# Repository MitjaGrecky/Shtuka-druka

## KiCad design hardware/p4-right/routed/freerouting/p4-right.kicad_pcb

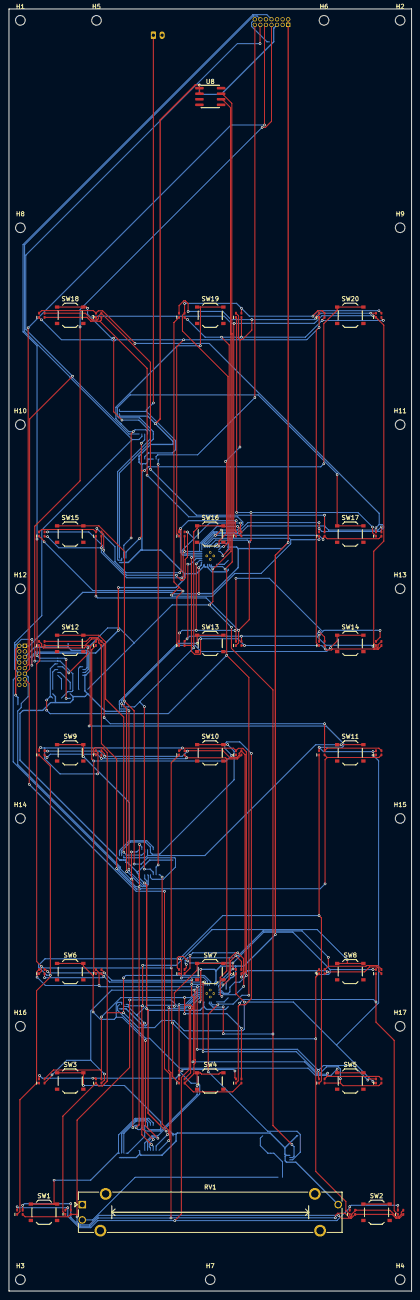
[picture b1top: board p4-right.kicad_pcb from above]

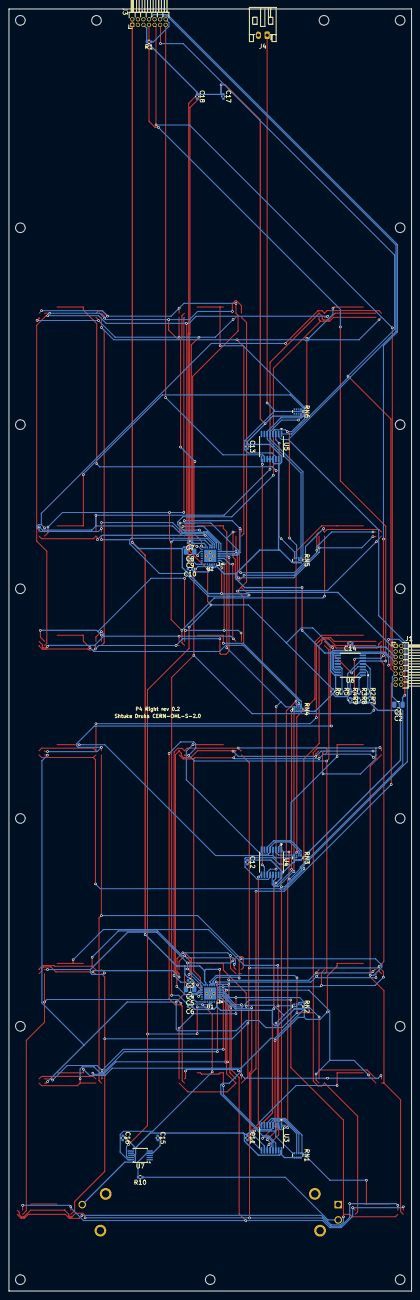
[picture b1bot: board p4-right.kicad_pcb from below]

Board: 2 copper layers, 92.0 x 293.0 mm, 123 parts (44 on the bottom side), 84 nets.

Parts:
C1: 10u; C_0805_2012Metric
C2, C3, C5, C7, C9, C18: 1u; C_0402_1005Metric
C4, C8: 4.7u; C_0805_2012Metric
C6, C10: 1n; C_0402_1005Metric
C11, C12, C13, C14, C15, C16, C17: 100n; C_0402_1005Metric
D1, D2, D3, D4, D5, D6, D7, D8, D9, D10, D11, D12, D13, D14, D15, D16, D17, D18, D19, D20, D21, D22, D23, D24, D25, D26, D27, D28, D29, D30, D31, D32, D33, D34, D35, D36, D37, D38, D39, D40: XL-1615RGBC-RF; LED_RGB_XL-1615RGBC_1.6x1.5mm
H1, H2, H3, H4, H5, H6, H7, H8, H9, H10, H11, H12, H13, H14, H15, H16, H17: M2; MountingHole_2.2mm_M2
J1: Deck bus to P2 2x8 1.27; PinHeader_2x08_P1.27mm_Horizontal
J3: Module bus to W3 2x7 1.27; PinHeader_2x07_P1.27mm_Horizontal
J4: Wheel push; JST_PH_S2B-PH-K_1x02_P2.00mm_Horizontal
R1, R2: 10k; R_0402_1005Metric
R3, R4, R5: 0; R_0402_1005Metric
R6, R7, R8, R9: 4.7k; R_0402_1005Metric
R10: 1k; R_0402_1005Metric
RN1, RN2, RN3, RN4, RN5, RN6: 4x10k; R_Array_Convex_4x0402
RV1: 10k lin, 45 mm travel; Potentiometer_Bourns_PTA4543_Single_Slide
SW1, SW2, SW3, SW4, SW5, SW6, SW7, SW8, SW9, SW10, SW11, SW12, SW13, SW14, SW15, SW16, SW17, SW18, SW19, SW20: TS-1187A-B-A-B; SW_Push_1P1T_XKB_TS-1187A
U1, U2: LP5864RSMR; VQFN-32-1EP_4x4mm_P0.4mm_EP2.8x2.8mm
U3, U4, U5: 74HC165PW; TSSOP-16_4.4x5mm_P0.65mm
U6: TCA9546APWR; TSSOP-16_4.4x5mm_P0.65mm
U7: ADS1115IDGSR; TSSOP-10_3x3mm_P0.5mm
U8: AS5600-ASOT; SOIC-8_3.9x4.9mm_P1.27mm

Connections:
+3V3: C2.1, C6.1, C10.1, C11.1, C12.1, C13.1, C14.1, C16.1, C17.1, C18.1, J1.5, J3.5, R1.2, R2.2, R4.2, R6.2, R7.2, R8.2, R9.2, RN1.5, RN1.6, RN1.7, RN1.8, RN2.5, RN2.6, RN2.7, RN2.8, RN3.5, RN3.6, RN3.7, RN3.8, RN4.5, RN4.6, RN4.7, RN4.8, RN5.5, RN5.6, RN5.7, RN5.8, RN6.8, RV1.3, U1.32, U2.30, U2.32, U3.16, U4.16, U5.11, U5.12, U5.13, U5.16, U6.16, U7.8, U8.1, U8.2
+5V: C1.1, C3.1, C4.1, C7.1, C8.1, J1.1, J1.2, J3.1, J3.2, U1.1, U1.15, U2.1, U2.15
/AIN0: C15.1, R10.2, U7.4
/A_CS0: D1.1, D2.1, D3.1, D4.1, U1.2
/A_CS1: D1.3, D2.3, D3.3, D4.3, U1.3
/A_CS2: D1.4, D2.4, D3.4, D4.4, U1.4
/A_CS3: D5.1, D6.1, D7.1, D8.1, U1.5
/A_CS4: D5.3, D6.3, D7.3, D8.3, U1.6
/A_CS5: D5.4, D6.4, D7.4, D8.4, U1.7
/A_CS6: D9.1, D10.1, D11.1, D12.1, U1.8
/A_CS7: D9.3, D10.3, D11.3, D12.3, U1.9
/A_CS8: D9.4, D10.4, D11.4, D12.4, U1.10
/A_CS9: D13.1, D14.1, D15.1, D16.1, U1.16
/A_CS10: D13.3, D14.3, D15.3, D16.3, U1.17
/A_CS11: D13.4, D14.4, D15.4, D16.4, U1.18
/A_CS12: D17.1, D18.1, D19.1, D20.1, U1.19
/A_CS13: D17.3, D18.3, D19.3, D20.3, U1.20
/A_CS14: D17.4, D18.4, D19.4, D20.4, U1.21
/A_CS15: D21.1, D22.1, D23.1, D24.1, U1.22
/A_CS16: D21.3, D22.3, D23.3, D24.3, U1.23
/A_CS17: D21.4, D22.4, D23.4, D24.4, U1.24
/A_SW0: D1.2, D5.2, D9.2, D13.2, D17.2, D21.2, U1.11
/A_SW1: D2.2, D6.2, D10.2, D14.2, D18.2, D22.2, U1.12
/A_SW2: D3.2, D7.2, D11.2, D15.2, D19.2, D23.2, U1.13
/A_SW3: D4.2, D8.2, D12.2, D16.2, D20.2, D24.2, U1.14
/A_VCAP: C5.1, U1.25
/BTN1: RN1.1, SW1.1, U3.6
/BTN2: RN1.2, SW2.1, U3.5
/BTN3: RN1.3, SW3.1, U3.4
/BTN4: RN1.4, SW4.1, U3.3
/BTN5: RN2.1, SW5.1, U3.14
/BTN6: RN2.2, SW6.1, U3.13
/BTN7: RN2.3, SW7.1, U3.12
/BTN8: RN2.4, SW8.1, U3.11
/BTN9: RN3.1, SW9.1, U4.6
/BTN10: RN3.2, SW10.1, U4.5
/BTN11: RN3.3, SW11.1, U4.4
/BTN12: RN3.4, SW12.1, U4.3
/BTN13: RN4.1, SW13.1, U4.14
/BTN14: RN4.2, SW14.1, U4.13
/BTN15: RN4.3, SW15.1, U4.12
/BTN16: RN4.4, SW16.1, U4.11
/BTN17: RN5.1, SW17.1, U5.6
/BTN18: RN5.2, SW18.1, U5.5
/BTN19: RN5.3, SW19.1, U5.4
/BTN20: RN5.4, SW20.1, U5.3
/B_CS0: D25.1, D26.1, D27.1, D28.1, U2.2
/B_CS1: D25.3, D26.3, D27.3, D28.3, U2.3
/B_CS2: D25.4, D26.4, D27.4, D28.4, U2.4
/B_CS3: D29.1, D30.1, D31.1, D32.1, U2.5
/B_CS4: D29.3, D30.3, D31.3, D32.3, U2.6
/B_CS5: D29.4, D30.4, D31.4, D32.4, U2.7
/B_CS6: D33.1, D34.1, D35.1, D36.1, U2.8
/B_CS7: D33.3, D34.3, D35.3, D36.3, U2.9
/B_CS8: D33.4, D34.4, D35.4, D36.4, U2.10
/B_CS9: D37.1, D38.1, D39.1, D40.1, U2.16
/B_CS10: D37.3, D38.3, D39.3, D40.3, U2.17
/B_CS11: D37.4, D38.4, D39.4, D40.4, U2.18
/B_SW0: D25.2, D29.2, D33.2, D37.2, U2.11
/B_SW1: D26.2, D30.2, D34.2, D38.2, U2.12
/B_SW2: D27.2, D31.2, D35.2, D39.2, U2.13
/B_SW3: D28.2, D32.2, D36.2, D40.2, U2.14
/B_VCAP: C9.1, U2.25
/MUX_A0: R3.1, U6.1
/MUX_A1: R4.1, U6.2
/MUX_A2: R5.1, U6.13
/MUX_RST: R2.1, U6.3
/SC0: R7.1, U1.28, U2.28, U6.5, U7.10, U8.7
/SC1: J3.8, R9.1, U6.7
/SCL: J1.8, U6.14
/SD0: R6.1, U1.29, U2.29, U6.4, U7.9, U8.6
/SD1: J3.7, R8.1, U6.6
/SDA: J1.7, U6.15
/SR_CLK: J1.12, J3.12, U3.2, U4.2, U5.2
/SR_END: J3.14, R1.1
/SR_OUT: J1.13, U3.9
/SR_Q1: U3.10, U4.9
/SR_Q2: U4.10, U5.9
/SR_W3: J3.13, U5.10
/WHEEL_PUSH: J4.1, RN6.1, U5.14
/XFADER: R10.1, RV1.2
/~INT: J1.9, J3.9
/~SR_LOAD: J1.11, J3.11, U3.1, U4.1, U5.1
GND: C1.2, C2.2, C3.2, C4.2, C5.2, C6.2, C7.2, C8.2, C9.2, C10.2, C11.2, C12.2, C13.2, C14.2, C15.2, C16.2, C17.2, C18.2, J1.3, J1.4, J1.6, J1.10, J1.16, J3.3, J3.4, J3.6, J3.10, J4.2, R3.2, R5.2, RV1.1, SW1.2, SW2.2, SW3.2, SW4.2, SW5.2, SW6.2, SW7.2, SW8.2, SW9.2, SW10.2, SW11.2, SW12.2, SW13.2, SW14.2, SW15.2, SW16.2, SW17.2, SW18.2, SW19.2, SW20.2, U1.26, U1.27, U1.30, U1.31, U1.33, U2.26, U2.27, U2.31, U2.33, U3.8, U3.15, U4.8, U4.15, U5.8, U5.15, U6.8, U7.1, U7.3, U7.5, U7.6, U7.7, U8.4, U8.8

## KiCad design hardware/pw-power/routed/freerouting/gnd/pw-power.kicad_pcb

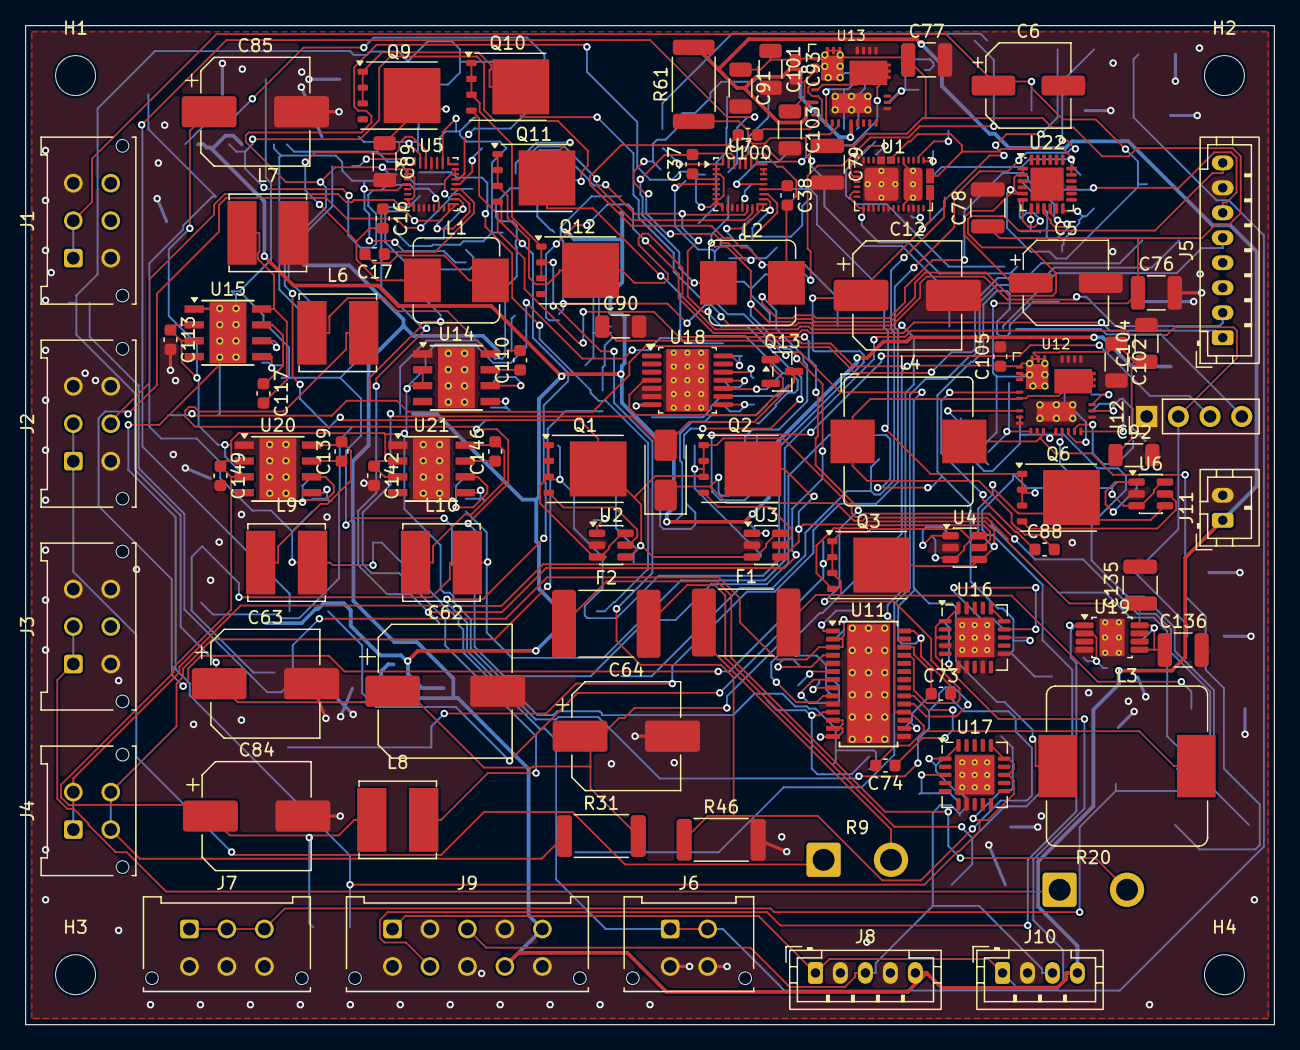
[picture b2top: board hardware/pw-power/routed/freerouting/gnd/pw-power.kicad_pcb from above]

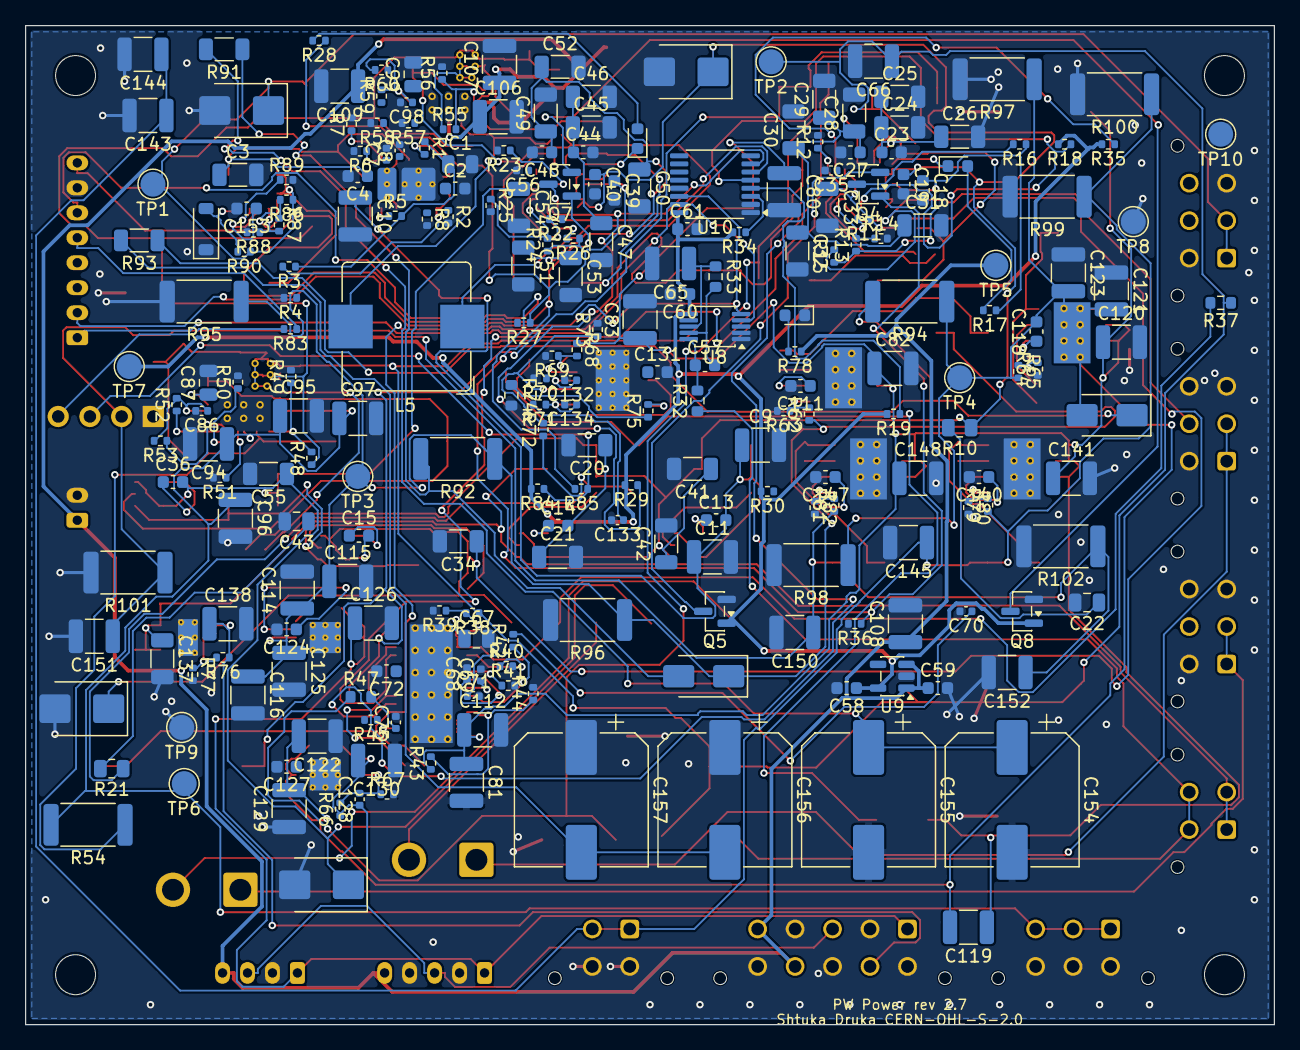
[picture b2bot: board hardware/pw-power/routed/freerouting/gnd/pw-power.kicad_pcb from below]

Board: 4 copper layers, 100.0 x 80.0 mm, 343 parts (243 on the bottom side), 177 nets.

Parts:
C1: 10u; C_0805_2012Metric
C2: 4.7u; C_0603_1608Metric
C3: 10u 50V; C_1206_3216Metric
C4, C93, C105, C153: 10n 50V; C_0603_1608Metric
C5, C6: 47u 35V; CP_Elec_6.3x5.9
C7, C8: 330p; C_0402_1005Metric
C9, C10, C114, C115, C116, C121, C122, C123, C143, C144, C145, C150, C151, C152: 22u 25V; C_1210_3225Metric
C11, C125, C126, C129: 10u 25V; C_1210_3225Metric
C12: 47u 35V; CP_Elec_8x10.5
C13, C14, C15, C27, C36, C48, C110, C117, C139, C146: 100n 25V; C_0603_1608Metric
C16, C17, C37, C38: 47n 25V; C_0603_1608Metric
C18, C39: 4.7u 10V; C_0603_1608Metric
C19, C23, C40, C44, C57, C73, C74: 100n 50V; C_0603_1608Metric
C20, C21, C24, C25, C26, C41, C42, C45, C46, C47: 10u 35V; C_1206_3216Metric
C22, C43: 2.2u 35V; C_0805_2012Metric
C28, C29, C30, C31, C32, C33, C34, C49, C50, C51, C52, C53, C54, C55: 10u 25V; C_1206_3216Metric
C35, C56: 1n 50V; C_0402_1005Metric
C58, C61: 100n; C_0603_1608Metric
C59, C60, C111, C118, C124, C127, C140, C147: 1u; C_0603_1608Metric
C62: 100u 35V; CP_Elec_10x10.5
C63, C64: 150u 35V; CP_Elec_8x10.5
C65, C66, C112, C119, C120, C141, C148: 10u 50V; C_1210_3225Metric
C67: 1u 50V; C_0805_2012Metric
C68: 220p; C_0402_1005Metric
C69, C86, C98: 100n; C_0402_1005Metric
C70: 33n; C_0402_1005Metric
C71: 560p; C_0402_1005Metric
C72, C131: 1u 25V; C_0603_1608Metric
C75: 47p; C_0402_1005Metric
C76, C77, C78, C79: 4.7u 50V; C_1210_3225Metric
C80, C81, C82, C83: 10u 35V; C_1210_3225Metric
C84, C85: 100u 35V; CP_Elec_8x10.5
C87, C99: 4.7u; C_0805_2012Metric
C88, C100: 47n; C_0603_1608Metric
C89, C90, C91, C92, C101, C102, C103, C104: 2.2u 50V; C_1206_3216Metric
C94, C95, C96, C97, C106, C107, C108, C109: 47u 10V; C_1210_3225Metric
C113, C142, C149: 220n 50V; C_0603_1608Metric
C128: 10n; C_0402_1005Metric
C130: 47u 25V; C_1210_3225Metric
C132: 47n; C_0402_1005Metric
C133: 22n; C_0402_1005Metric
C134: 470p; C_0402_1005Metric
C135, C136, C138: 4.7u 100V; C_1210_3225Metric
C137: 1u 100V; C_1206_3216Metric
C154, C155, C156, C157: 470u 25V; CP_Elec_10x10.5
D1, D2: SMBJ20CA; D_SMB
D3, D5: SMBJ13CA; D_SMB
D4, D6, D8: green; LED_0603_1608Metric
D7: SS1H10; D_SMA
D9: BZT52C3V3; D_SOD-123
D10, D11: SS34; D_SMA
F1, F2: 10A; Fuse_2920_7451Metric
H1, H2, H3, H4: M3; MountingHole_3.2mm_M3_ISO7380
J1: USB-C Power in; Molex_Micro-Fit_3.0_43045-0612_2x03_P3.00mm_Vertical
J2: Battery 1; Molex_Micro-Fit_3.0_43045-0612_2x03_P3.00mm_Vertical
J3: Battery 2; Molex_Micro-Fit_3.0_43045-0612_2x03_P3.00mm_Vertical
J4: On/Off switch; Molex_Micro-Fit_3.0_43045-0412_2x02_P3.00mm_Vertical
J5: Power telemetry to P2; JST_PH_B8B-PH-K_1x08_P2.00mm_Vertical
J6: 15 V to H5; Molex_Micro-Fit_3.0_43045-0412_2x02_P3.00mm_Vertical
J7: +5V panel; Molex_Micro-Fit_3.0_43045-0612_2x03_P3.00mm_Vertical
J8: to R2; JST_PH_B5B-PH-K_1x05_P2.00mm_Vertical
J9: to A1/R1; Molex_Micro-Fit_3.0_43045-1012_2x05_P3.00mm_Vertical
J10: to F1; JST_PH_B4B-PH-K_1x04_P2.00mm_Vertical
J11: +5V screen; JST_PH_B2B-PH-K_1x02_P2.00mm_Vertical
J12: Fan 12 V PWM; PinHeader_1x04_P2.54mm_Vertical
L1, L2: 1uH; L_Bourns_SRP7028A_7.3x6.6mm
L3: 4.7uH; L_Bourns_SRP1245A
L4, L5: 4.7uH; L_Bourns_SRP1038C_10.0x10.0mm
L6, L7, L9, L10: 10uH; L_Bourns_SRN6045TA
L8: 22uH; L_Bourns_SRN6045TA
Q1, Q2, Q3, Q6, Q9, Q10, Q11, Q12: CSD18532Q5B; TDSON-8-1
Q4, Q5, Q7, Q8: 2N7002; SOT-23
Q13: IRLML0100; SOT-23
R1, R3: 42.2k; R_0402_1005Metric
R2, R4, R5, R6, R7, R8, R18, R19, R29, R30, R34, R35, R42, R45, R71, R73, R77, R84: 10k; R_0402_1005Metric
R9, R20: 0 wire 1mm2; SolderWire-1sqmm_1x02_P5.4mm_D1.4mm_OD2.7mm
R10, R21: 2; R_0805_2012Metric
R11, R22, R75, R83, R85: 100; R_0402_1005Metric
R12, R23: 10.5k; R_0402_1005Metric
R13, R24: 47k; R_0402_1005Metric
R14, R16, R25, R27, R36, R53, R60, R62, R64, R68, R79, R81: 100k; R_0402_1005Metric
R15, R26: 9.31k; R_0402_1005Metric
R17, R28, R78: 2.2k; R_0402_1005Metric
R31: 5m; R_2512_6332Metric
R32, R33, R37: 10; R_0603_1608Metric
R38: 249k; R_0402_1005Metric
R39: 32.4k; R_0402_1005Metric
R40: 93.1k; R_0402_1005Metric
R41: 27.4k; R_0402_1005Metric
R43: 453k; R_0402_1005Metric
R44: 20k; R_0402_1005Metric
R46: 8m; R_2512_6332Metric
R47: 100; R_0603_1608Metric
R48, R55: 392k; R_0402_1005Metric
R49, R56, R70: 49.9k; R_0402_1005Metric
R50, R57: 54.9k; R_0402_1005Metric
R51, R58: 41.2k; R_0402_1005Metric
R52, R59: 24.9k; R_0402_1005Metric
R54, R61: 6.8m; R_2512_6332Metric
R63, R65: 7.68k; R_0402_1005Metric
R66: 102k; R_0402_1005Metric
R67: 11k; R_0402_1005Metric
R69: 27k; R_0402_1005Metric
R72: 475k; R_0402_1005Metric
R74: 0.1; R_0603_1608Metric
R76: 383k; R_0402_1005Metric
R80: 7.15k; R_0402_1005Metric
R82: 9.09k; R_0402_1005Metric
R86: 357k; R_0402_1005Metric
R87: 118k; R_0402_1005Metric
R88: 26.7k; R_0402_1005Metric
R89: 3.32k; R_0402_1005Metric
R90: 220k; R_0402_1005Metric
R91, R93: 0; R_1206_3216Metric
R92, R94: 10; R_2512_6332Metric
R95, R96, R97, R98, R99, R100: 1k; R_2512_6332Metric
R101, R102: 820; R_2512_6332Metric
TP1: VBUS; TestPoint_Pad_D2.0mm
TP2: BUS; TestPoint_Pad_D2.0mm
TP3: P14; TestPoint_Pad_D2.0mm
TP4: N14; TestPoint_Pad_D2.0mm
TP5: +5V; TestPoint_Pad_D2.0mm
TP6: +5V_PANEL; TestPoint_Pad_D2.0mm
TP7: +3V3; TestPoint_Pad_D2.0mm
TP8, TP9, TP10: GND; TestPoint_Pad_D2.0mm
U1: TPS25730D; Texas_REF0038A_WQFN-38-2EP_6x4mm_P0.4
U2, U3, U4, U6: LM74700-Q1; SOT-23-6
U5, U7: BQ25798; Texas_RQM0029A_VQFN-29_4x4mm_P0.4mm
U8: INA226; MSOP-10_3x3mm_P0.5mm
U9: AP2112K-3.3; SOT-23-5
U10: TCA9546APW; TSSOP-16_4.4x5mm_P0.65mm
U11: LM5176; HTSSOP-28-1EP_4.4x9.7mm_P0.65mm_EP3.4x9.5mm_ThermalVias
U12, U13: LM70660; VQFN-29_RRX0029B_6x6_P0.5mm
U14, U15, U20, U21: LMR33640; Texas_HSOP-8-1EP_3.9x4.9mm_P1.27mm_ThermalVias
U16: TPS7A4701; Texas_RGW0020A_VQFN-20-1EP_5x5mm_P0.65mm_EP3.15x3.15mm_Ther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
U17: TPS7A3301; Texas_RGW0020A_VQFN-20-1EP_5x5mm_P0.65mm_EP3.15x3.15mm_Ther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
U18: LM5156H; Texas_HTSSOP-14-1EP_4.4x5mm_P0.65mm_EP3.4x5mm_Mask3.155x3.2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
U19: TPS7A4101; Texas_DGN0008B_VSSOP-8-1EP_3x3mm_P0.65mm_EP2x3mm_Mask1.88x1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
U22: TPS26631RGER; QFN-24-1EP_4x4mm_P0.5mm_EP2.65x2.65mm

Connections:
+3V3: C58.1, C60.1, C61.1, Q5.1, Q8.1, R18.2, R19.2, R29.2, R30.2, R34.2, R35.2, R84.2, TP7.1, U8.6, U9.5, U10.16
+5V: C59.1, C106.1, C107.1, C108.1, C109.1, J8.5, J9.5, J9.9, J10.4, J11.1, R61.2, R78.1, TP5.1, U9.1, U9.3, U13.6, U13.12
/+5V_PANEL: C94.1, C95.1, C96.1, C97.1, J7.1, J7.2, J7.3, R54.2, TP6.1, U12.6, U12.12
/+12V: C126.1, J8.1, J9.1, J10.1, U16.1, U16.3, U16.20
/+48V: C138.1, J9.7, R76.1, U19.1
/-12V: C128.1, C130.2, J8.3, J9.3, J10.3, R66.1, U17.1, U17.20
/B19_BOOT1: C73.1, U11.26
/B19_BOOT2: C74.1, U11.20
/B19_CMP_RC: C70.1, R42.2
/B19_COMP: C71.1, R42.1, U11.9
/B19_CS: C75.1, R47.2, U11.16
/B19_CSN: Q10.1, Q10.2, Q10.3, Q12.1, Q12.2, Q12.3, R46.1, R47.1
/B19_FB: R43.2, R44.1, U11.11
/B19_HDRV1: Q9.4, U11.27
/B19_HDRV2: Q11.4, U11.19
/B19_LDRV1: Q10.4, U11.25
/B19_LDRV2: Q12.4, U11.21
/B19_MODE: R40.1, U11.4
/B19_PG: R45.1, U11.17
/B19_RT: R41.1, U11.6
/B19_SLOPE: C68.1, U11.7
/B19_SS: C69.1, U11.8
/B19_SW1: C73.2, L3.1, Q9.1, Q9.2, Q9.3, Q10.5, U11.28
/B19_SW2: C74.2, L3.2, Q11.1, Q11.2, Q11.3, Q12.5, U11.18
/B19_UVLO: R38.2, R39.1, U11.1
/B19_VCC: C72.1, R45.2, U11.23
/B19_VIN: C67.1, R37.2, U11.2, U11.3
/BAT1_F: C15.2, C33.1, C34.1, D3.1, F1.2, Q3.1, Q3.2, Q3.3, R11.1, U4.3, U4.6, U5.22, U5.23
/BAT1_J: F1.1, R9.2
/BAT1_RAW: J2.1, J2.2, R9.1
/BAT2_F: C36.2, C54.1, C55.1, D5.1, F2.2, Q6.1, Q6.2, Q6.3, R22.1, U6.3, U6.6, U7.22, U7.23
/BAT2_J: F2.1, R20.2
/BAT2_RAW: J3.1, J3.2, R20.1
/BUS: C62.1, C63.1, C64.1, C65.1, C66.1, C76.1, C77.1, C78.1, C79.1, C89.1, C90.1, C91.1, C92.1, C93.1, C101.1, C102.1, C103.1, C104.1, C105.1, Q9.5, R31.2, R33.1, R37.1, R38.1, R48.1, R55.1, TP2.1, U8.8, U12.1, U12.2, U12.3, U12.27, U12.28, U12.29, U13.1, U13.2, U13.3, U13.27, U13.28, U13.29
/BUS_IN: J4.1, J4.2, Q2.5, Q3.5, Q6.5, U3.4, U4.4, U6.4
/BUS_SW: J4.3, J4.4, R31.1, R32.1
/CH1_BATP: R11.2, U5.18
/CH1_BTST1: C16.1, U5.4
/CH1_BTST2: C17.1, U5.19
/CH1_CE: Q4.3, R16.2, U5.13
/CH1_CEM: Q4.2, Q5.3
/CH1_ILIM: R13.2, R14.1, U5.17
/CH1_LEDA: D4.2, R17.2
/CH1_PMID: C23.1, C24.1, C25.1, C26.1, U5.29
/CH1_PROG: R12.1, U5.20
/CH1_REGN: C18.1, R13.1, R15.1, R16.1, R17.1, U5.5
/CH1_SCL: R18.1, U5.14, U10.5
/CH1_SDA: R19.1, U5.15, U10.4
/CH1_SDRV: C35.1, U5.24
/CH1_SNUB: C22.1, R10.2
/CH1_STAT: D4.1, U5.1
/CH1_SW1: C16.2, L1.1, U5.28
/CH1_SW2: C17.2, L1.2, U5.26
/CH1_SYS: C27.1, C28.1, C29.1, C30.1, C31.1, C32.1, U5.25
/CH1_TS: J2.5, R15.2, U5.16
/CH2_BATP: R22.2, U7.18
/CH2_BTST1: C37.1, U7.4
/CH2_BTST2: C38.1, U7.19
/CH2_CE: Q7.3, R27.2, U7.13
/CH2_CEM: Q7.2, Q8.3
/CH2_ILIM: R24.2, R25.1, U7.17
/CH2_LEDA: D6.2, R28.2
/CH2_PMID: C44.1, C45.1, C46.1, C47.1, U7.29
/CH2_PROG: R23.1, U7.20
/CH2_REGN: C39.1, R24.1, R26.1, R27.1, R28.1, U7.5
/CH2_SCL: R29.1, U7.14, U10.7
/CH2_SDA: R30.1, U7.15, U10.6
/CH2_SDRV: C56.1, U7.24
/CH2_SNUB: C43.1, R21.2
/CH2_STAT: D6.1, U7.1
/CH2_SW1: C37.2, L2.1, U7.28
/CH2_SW2: C38.2, L2.2, U7.26
/CH2_SYS: C48.1, C49.1, C50.1, C51.1, C52.1, C53.1, U7.25
/CH2_TS: J3.5, R26.2, U7.16
/CHG_EN: J5.8, Q4.1, Q7.1, R36.1
/CHG_INT: J5.4, R35.1, U5.21, U7.21
/EXT: C14.2, C19.1, C20.1, C21.1, C40.1, C41.1, C42.1, D2.1, Q1.5, Q2.1, Q2.2, Q2.3, R10.1, R21.1, U2.4, U3.3, U3.6, U5.2, U5.3, U5.8, U5.9, U7.2, U7.3, U7.8, U7.9
/FAN_PWM: J12.4, R83.2
/FAN_PWM_IN: J5.5, R83.1
/FAN_TACH: J12.3, R84.1, R85.1
/FAN_TACH_OUT: J5.6, R85.2
/HV_COMP: C134.1, R71.1, U18.8
/HV_CRC: C133.1, R71.2
/HV_CS: R75.2, U18.7
/HV_CSN: Q13.2, R74.1, R75.1
/HV_FB: R72.2, R73.1, U18.10
/HV_GATE: Q13.1, U18.4
/HV_RAW: C135.1, C136.1, C137.1, D7.1, R72.1, U19.5, U19.8
/HV_RT: R70.1, U18.12
/HV_SS: C132.1, U18.11
/HV_SW: D7.2, L8.2, Q13.3
/HV_UVLO: R68.2, R69.1, U18.14
/HV_VCC: C131.1, U18.3, U18.9
/IBAT1_GATE: Q3.4, U4.5
/IBAT1_VCAP: C15.1, U4.1
/IBAT2_GATE: Q6.4, U6.5
/IBAT2_VCAP: C36.1, U6.1
/IEXT_GATE: Q2.4, U3.5
/IEXT_VCAP: C14.1, U3.1
/IPD_GATE: Q1.4, U2.5
/IPD_VCAP: C13.1, U2.1
/LED_K: D8.2, R78.2
/MUX_RST: R34.1, U10.3
/N12_FB: C128.2, R66.2, R67.1, U17.3
/N12_NR: C127.1, U17.14
/N14: C118.2, C119.2, C121.2, C122.2, C123.2, C129.2, D11.2, R65.2, R94.1, R97.1, R98.1, TP4.1, U15.1, U15.9, U17.13, U17.15, U17.16
/N14_BOOT: C117.1, U15.7
/N14_C: C156.2, C157.2, R93.2
/N14_FB: R64.2, R65.1, U15.5
/N14_ST: D11.1, R93.1, R94.2
/N14_SW: C117.2, L7.1, U15.8
/N14_VCC: C118.1, U15.6
/P5VPANEL_BOOT: C88.1, U12.4
/P5VPANEL_CFG: R51.1, U12.13
/P5VPANEL_EN: R48.2, R49.1, U12.9
/P5VPANEL_FB: R52.1, U12.16
/P5VPANEL_LS: L4.2, R54.1, U12.11
/P5VPANEL_RT: R50.1, U12.14
/P5VPANEL_SW: C88.2, L4.1, U12.5, U12.20, U12.21, U12.22
/P5VPANEL_VCC: C87.1, U12.19
/P5VPANEL_VDDA: C86.1, R52.2, R53.2, U12.18
/P5VPANEL_XC: R53.1, U12.15
/P5V_BOOT: C100.1, U13.4
/P5V_CFG: R58.1, U13.13
/P5V_EN: R55.2, R56.1, U13.9
/P5V_FB: R59.1, U13.16
/P5V_LS: L5.2, R61.1, U13.11
/P5V_RT: R57.1, U13.14
/P5V_SW: C100.2, L5.1, U13.5, U13.20, U13.21, U13.22
/P5V_VCC: C99.1, U13.19
/P5V_VDDA: C98.1, R59.2, R60.2, U13.18
/P5V_XC: R60.1, U13.15
/P12_NR: C124.1, U16.14
/P14: C114.1, C115.1, C116.1, C125.1, D10.1, L6.2, R62.1, R92.1, R95.1, R96.1, TP3.1, U16.13, U16.15, U16.16
/P14_BOOT: C110.1, U14.7
/P14_C: C154.1, C155.1, R91.2
/P14_FB: R62.2, R63.1, U14.5
/P14_ST: D10.2, R91.1, R92.2
/P14_SW: C110.2, L6.1, U14.8
/P14_VCC: C111.1, U14.6
/P48_FB: R76.2, R77.1, U19.2
/PDF_DVDT: C153.1, U22.9
/PDF_ILIM: R89.1, U22.10
/PDF_OV: R87.2, R88.1, U22.7
/PDF_SHDN: D9.2, R90.2, U22.12
/PDF_UV: R86.2, R87.1, U22.6
/PD_ADCIN1: R1.2, R2.1, U1.2
/PD_ADCIN34: R3.2, R4.1, U1.5, U1.7
/PD_CC1: C7.1, J1.5, U1.28
/PD_CC2: C8.1, J1.6, U1.29
/PD_DRAIN: U1.15, U1.30, U1.40
/PD_FAULT: R5.1, U1.18
/PD_LDO1V5: C2.1, U1.4
/PD_LDO3V3: C1.1, R1.1, R3.1, R5.2, U1.1, U1.3
/PD_OUT: C9.1, C10.1, C11.1, C12.1, C13.2, Q1.1, Q1.2, Q1.3, U1.20, U2.3, U2.6
/PD_RSV26: R6.1, U1.26
/PD_RSV27: R7.1, U1.27
/PD_RSV36: R8.1, U1.36
/PD_VBUS: C5.1, C6.1, D1.1, J1.1, J1.2, R86.1, R90.1, TP1.1, U22.1, U22.2, U22.5
/PD_VBUSF: C3.1, C4.1, U1.23, U1.32, U22.17, U22.18
/PM_ALERT: J5.3, U8.3
/PM_INN: C57.2, R33.2, U8.9
/PM_INP: C57.1, R32.2, U8.10
/PM_SCL: J5.2, U8.5, U10.14
/PM_SDA: J5.1, U8.4, U10.15
/V12F: C150.1, C151.1, C152.1, J12.2, L10.2, R81.1, R101.1, R102.1
/V12F_BOOT: C146.1, U21.7
/V12F_FB: R81.2, R82.1, U21.5
/V12F_SW: C146.2, L10.1, U21.8
/V12F_VCC: C147.1, U21.6
/V15: C143.1, C144.1, C145.1, J6.1, J6.2, L9.2, R79.1, R99.1, R100.1
/V15_BOOT: C139.1, U20.7
/V15_FB: R79.2, R80.1, U20.5
/V15_SW: C139.2, L9.1, U20.8
/V15_VCC: C140.1, U20.6
/V19: C80.1, C81.1, C82.1, C83.1, C84.1, C85.1, C112.1, C113.1, C119.1, C120.1, C141.1, C142.1, C148.1, C149.1, L8.1, Q11.5, R43.1, R68.1, U11.12, U11.13, U11.14, U11.24, U14.2, U14.3, U15.2, U15.3, U18.1, U20.2, U20.3, U21.2, U21.3
GND: C1.2, C2.2, C3.2, C4.2, C5.2, C6.2, C7.2, C8.2, C9.2, C10.2, C11.2, C12.2, C18.2, C19.2, C20.2, C21.2, C22.2, C23.2, C24.2, C25.2, C26.2, C27.2, C28.2, C29.2, C30.2, C31.2, C32.2, C33.2, C34.2, C35.2, C39.2, C40.2, C41.2, C42.2, C43.2, C44.2, C45.2, C46.2, C47.2, C48.2, C49.2, C50.2, C51.2, C52.2, C53.2, C54.2, C55.2, C56.2, C58.2, C59.2, C60.2, C61.2, C62.2, C63.2, C64.2, C65.2, C66.2, C67.2, C68.2, C69.2, C70.2, C71.2, C72.2, C75.2, C76.2, C77.2, C78.2, C79.2, C80.2, C81.2, C82.2, C83.2, C84.2, C85.2, C86.2, C87.2, C89.2, C90.2, C91.2, C92.2, C93.2, C94.2, C95.2, C96.2, C97.2, C98.2, C99.2, C101.2, C102.2, C103.2, C104.2, C105.2, C106.2, C107.2, C108.2, C109.2, C111.2, C112.2, C113.2, C114.2, C115.2, C116.2, C120.2, C121.1, C122.1, C123.1, C124.2, C125.2, C126.2, C127.2, C129.1, C130.1, C131.2, C132.2, C133.2, C134.2, C135.2, C136.2, C137.2, C138.2, C140.2, C141.2, C142.2, C143.2, C144.2, C145.2, C147.2, C148.2, C149.2, C150.2, C151.2, C152.2, C153.2, C154.2, C155.2, C156.1, C157.1, D1.2, D2.2, D3.2, D5.2, D8.1, D9.1, J1.3, J1.4, J2.3, J2.4, J2.6, J3.3, J3.4, J3.6, J5.7, J6.3, J6.4, J7.4, J7.5, J7.6, J8.2, J8.4, J9.2, J9.4, J9.6, J9.8, J9.10, J10.2, J11.2, J12.1, L7.2, Q5.2, Q8.2, R2.2, R4.2, R6.2, R7.2, R8.2, R12.2, R14.2, R23.2, R25.2, R36.2, R39.2, R40.2, R41.2, R44.2, R46.2, R49.2, R50.2, R51.2, R56.2, R57.2, R58.2, R63.2, R64.1, R67.2, R69.2, R70.2, R73.2, R74.2, R77.2, R80.2, R82.2, R88.2, R89.2, R95.2, R96.2, R97.2, R98.2, R99.2, R100.2, R101.2, R102.2, TP8.1, TP9.1, TP10.1, U1.8, U1.9, U1.11, U1.12, U1.14, U1.16, U1.17, U1.31, U1.34, U1.38, U1.39, U2.2, U3.2, U4.2, U5.10, U5.11, U5.27, U6.2, U7.10, U7.11, U7.27, U8.1, U8.2, U8.7, U9.2, U10.1, U10.2, U10.8, U10.13, U11.5, U11.10, U11.15, U11.22, U11.29, U12.8, U12.17, U12.23, U12.24, U12.25, U12.26, U12.30, U13.8, U13.17, U13.23, U13.24, U13.25, U13.26, U13.30, U14.1, U14.9, U16.4, U16.6, U16.7, U16.9, U16.11, U16.21, U17.7, U17.21, U18.5, U18.6, U18.15, U19.4, U19.9, U20.1, U20.9, U21.1, U21.9, U22.8, U22.11, U22.15, U22.25

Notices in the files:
hardware/p4-right/routed/freerouting/p4-right.kicad_pcb:
Shtuka Druka - open hardware, CERN-OHL-S-2.0
Shtuka Druka CERN-OHL-S-2.0
